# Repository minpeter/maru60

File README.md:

# Maru60

Maru60 is an experimental HHKB housing for Rule 60 V3 internals with an
integrated honeycomb wrist rest. This repository also includes the standalone
Rule 60 V3 wrist rest and an unfinished RP2350A PCB design.

| Start here | Contents |
| --- | --- |
| [Housing](docs/housing.md) | Build and verify matching top/bottom variants; print files, fit and assembly |
| [Physical build 02 — v7.15](docs/print-history.md) | Owner-designated second physical build: 6095, stock catches, inserts; final print pair and change record |
| [Standalone wrist rest](docs/wrist-rest.md) | Current tight-fit downloads, reproduction and print guidance |
| [PCB current state](pcb/CURRENT.md) | Strict baseline, development prototype and unresolved qualification |
| [PCB validation](docs/pcb-validation.md) | Reproduce native CAD, portable firmware and power checks |
| [PCB order package](pcb/order/README.md) | Gerbers, JLCPCB BOM and placement file for the order candidate, with ordering steps |
| [PCB fabrication draft](pcb/fabrication/README.md) | Earlier BOM, CPL and Gerbers for the 0/0 prototype; superseded by the order package |
| [Detailed fabrication reference](docs/fabrication.md) | Complete design history, measurements, hardware and plate guidance |

Install [uv](https://docs.astral.sh/uv/), then run from the repository root:

```sh
uv sync --locked
uv run python -m maru60.pipeline --board ph60-rev3
uv run python -m unittest discover -s tests
uv run tools/check_pcb_current.py
```

The housing pipeline builds and verifies both cases in a variant-specific
folder under `build/`. Both cases default to `--catches stock` with M2
self-tapping screw pilots (`--no-inserts`). Add `--catches luban32` for the
compatible LUBAN 32 mm ball catches (assumed widths, caliper first), `--inserts`
for CANOT M2 OD3.5 x L3 heat-set insert bores in both cases, or
`--no-battery-bay` for the wired lower case. Published `models/` and `evidence/`
change only with `--publish`; review [housing guidance](docs/housing.md) first.
CAD checks do not establish physical fit or strength. The custom PCB has an
[order candidate](pcb/order/README.md) for a first prototype run; it has **not
been built or qualified on hardware**.

The standalone wrist rest uses [CC BY 4.0](LICENSE); the Maru60 cases use
[CC BY-NC 4.0](LICENSE-topcase). See the [full license and design history](docs/fabrication.md#license-and-design-history)
for third-party exceptions and attribution.

<details>
<summary>Earlier README section links</summary>

[Rule 60 V3 Honeycomb Wrist Rest — No Extra Hardware](docs/fabrication.md#rule-60-v3-honeycomb-wrist-rest--no-extra-hardware) · 
[Download and print](docs/fabrication.md#download-and-print) · 
[Fit and assembly](docs/fabrication.md#fit-and-assembly) · 
[Slicing](docs/fabrication.md#slicing) · 
[Reproduce and continue designing](docs/fabrication.md#reproduce-and-continue-designing) · 
[Verification and limitations](docs/fabrication.md#verification-and-limitations) · 
[Maru60 HHKB top case with integrated wrist rest (experimental)](docs/fabrication.md#maru60-hhkb-top-case-with-integrated-wrist-rest-experimental) · 
[Printing](docs/fabrication.md#printing) · 
[Interface spec and PCB boards](docs/fabrication.md#interface-spec-and-pcb-boards) · 
[Reproduce](docs/fabrication.md#reproduce) · 
[Optional upper strike inserts (CANOT OD3.5 × L3 trial)](docs/fabrication.md#optional-upper-strike-inserts-canot-od35--l3-trial) · 
[Measurements and evidence](docs/fabrication.md#measurements-and-evidence) · 
[Verification and limitations](docs/fabrication.md#verification-and-limitations-1) · 
[Maru60 HHKB bottom case (draft)](docs/fabrication.md#maru60-hhkb-bottom-case-draft) · 
[Local M2 insert-mount study (not released)](docs/fabrication.md#local-m2-insert-mount-study-not-released) · 
[Purchased 32 mm catches / CANOT inserts — separate local trial](docs/fabrication.md#purchased-32-mm-catches--canot-inserts--separate-local-trial) · 
[Photo-refined sculpted alternative (C-derived, still experimental)](docs/fabrication.md#photo-refined-sculpted-alternative-c-derived-still-experimental) · 
[HHKB gasket plate (INKC drawing)](docs/fabrication.md#hhkb-gasket-plate-inkc-drawing) · 
[PCB](docs/fabrication.md#pcb) · 
[Off-the-shelf board: PH60 Rev.3 Multi](docs/fabrication.md#off-the-shelf-board-ph60-rev3-multi) · 
[Maru60's own PCB (RP2350A, work in progress)](docs/fabrication.md#maru60s-own-pcb-rp2350a-work-in-progress) · 
[License and design history](docs/fabrication.md#license-and-design-history)

</details>

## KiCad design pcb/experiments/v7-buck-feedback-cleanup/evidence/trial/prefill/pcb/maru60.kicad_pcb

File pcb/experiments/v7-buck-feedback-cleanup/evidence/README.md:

# BUCK_FB dead-arm experiment: UNSELECTED, strict global plane gate FAIL

This packet preserves the exact selected 2c7 source project, unselected aead dead-arm cleanup, native prefill/filled diagnostics, source-bound plan, independent strict rejection, and separate no-edit/repeat normal-refill controls. No selection, tolerance waiver, manual fill repair, noise reduction, loop-stability, hardware or manufacturing qualification is implied.

Read trial/TECHNICAL_REVIEW.md first. The independent-strict-review packet is included unchanged with its own manifest. Read CASE_SPECIFIC_ENGINEERING_DECISION.md for the separate case-specific precision condition. It does not retroactively change the original strict rejection; independent precision proof and fresh final rechecks are separate evidence. Both normal-refill controls are byte-identical fixed points; the real remote saved-contour losses remain.

Scripts preserve their original absolute paths and exact source-hash assertions. For replay on another machine, map the original /tmp/v7-buck-deadarm-trial-2c7e to trial/, the plan and control directories to the corresponding bundled folders, and the selected repository project to trial/source/pcb/. KiCad 9.0.2+dfsg-1 and Python pcbnew are required. Runtime caches are excluded; native evidence and failed/interrupted diagnostic records are retained. Do not replay scripts against the selected project without isolation. The source-bound CAD is supplied directly, not reconstructed from a report.

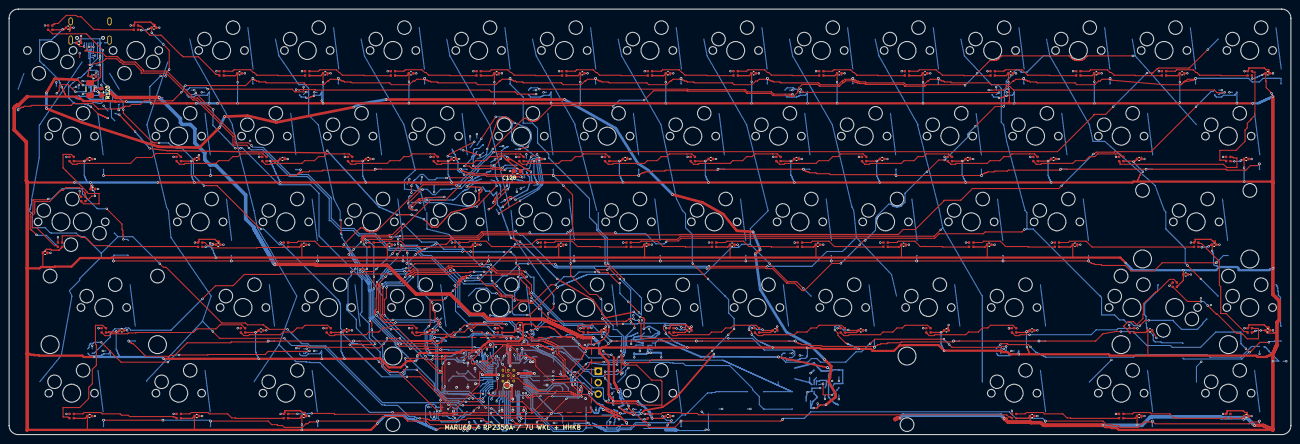
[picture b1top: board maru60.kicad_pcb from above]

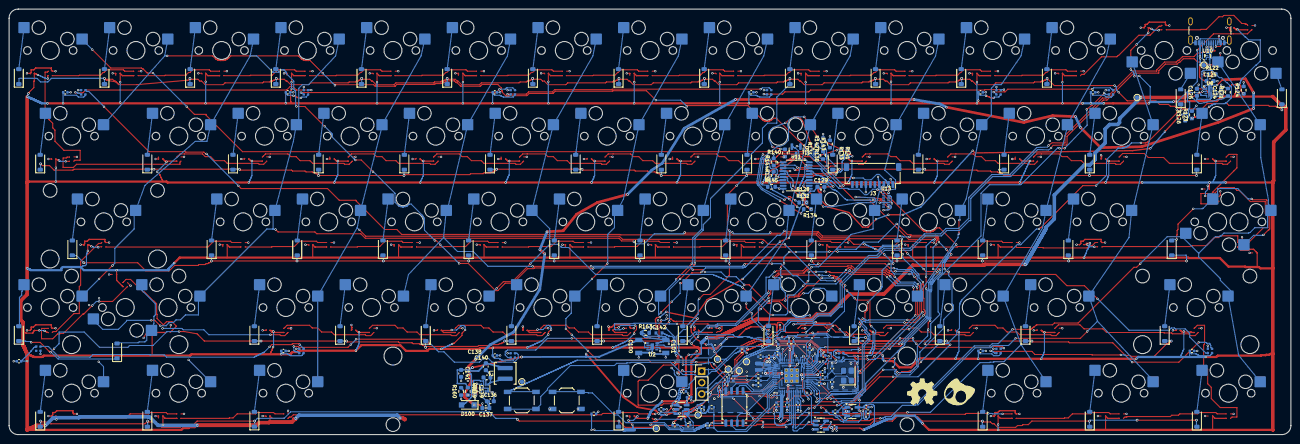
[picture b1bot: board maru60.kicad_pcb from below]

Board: 4 copper layers, 285.0 x 94.6 mm, 382 parts (247 on the bottom side), 224 nets.

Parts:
C100, C101: 4.7uF 50V X7R 10%; Murata_GRM31_1206_Reflow_1.0x1.6_Gap1.9
C102, C103: 4.7u 6.3V; C_0402_Official_R4_Wide
C104: 4.7u 6.3V; C_0402_1005Metric
C105, C108, C110, C111, C112, C113, C114, C115, C116, C117, C118, C122, C123, C199: 100n; C_0402_1005Metric
C106, C107: 15p C0G; C_0402_1005Metric
C109: 4.7u 6.3V X5R; C_0402_1005Metric
C120: 1u; C_0402_1005Metric
C121: 4.7u; C_0402_1005Metric
C124: 10nF 10% 50V; C_0603_1608Metric
C125: 1uF 50V effective TBD; C_0603_1608Metric
C126: 1uF 50V; C_0603_1608Metric
C128, C129: 100nF 16V; C_0603_1608Metric
C136: 100nF 50V; C_0603_1608Metric
C137: 4.7uF 50V effective>=2uF TBD; C_0603_1608Metric
C138: 100nF 16V BST-SW; C_0603_1608Metric
C139: 100nF 10% 16V - soft start; C_0603_1608Metric
C140, C141: 22uF 10V effective>=12uF TBD; C_0603_1608Metric
C142: 10nF 50V C0G 5%; Murata_GRM18_0603_Reflow_0.65x0.75_Gap0.7
C200, C201, C202, C203, C204, C205, C206, C207, C208, C209, C210, C211, C212, C213, C214, C215, C216, C217, C218, C219, C220, C221, C222, C223, C224, C225, C226, C227, C228, C229, C230, C231, C232, C233, C234, C235, C236, C237, C238, C239, C240, C241, C242, C243, C244, C245, C246, C247, C248, C249, C250, C251, C252, C253, C254, C255, C256, C257, C258, C259, C260, C261, C262, C263, C264, C265, C266, C267, C268, C269, C270, C271, C272, C273: 100nF; C_0402_1005Metric
C274, C275: 100nF 10V X7R candidate; C_0402_1005Metric
D1, D2, D3, D4, D5, D6, D7, D8, D9, D10, D11, D12, D13, D14, D15, D16, D17, D18, D19, D20, D21, D22, D23, D24, D25, D26, D27, D28, D29, D30, D31, D32, D33, D34, D35, D36, D37, D38, D39, D40, D41, D42, D43, D44, D45, D46, D47, D48, D49, D50, D51, D52, D53, D54, D55, D56, D57, D58, D59, D60, D61, D62: 1N4148W; D_SOD-123
D100: PMEG4030ER - reverse discharge bypass; Nexperia_CFP3_SOD-123W
F1: SF-1206F100-2 CANDIDATE; Fuse_1206_3216Metric
J1: USB4105-GF-A (candidate); USB_C_Receptacle_GCT_USB4105-xx-A_16P_TopMnt_Horizontal
J2: SWD / GND / SWCLK; PinHeader_1x03_P2.54mm_Vertical
J3: SM10B-SRSS-TB; JST_SH_SM10B-SRSS-TB_1x10-1MP_P1.00mm_Horizontal
L1: 3.3uH AOTA-B201610S3R3-101-T; Abracon_AOTA_B201610S3R3_Official_R4
L2: XAL4030-472MEC 4.7uH 20%; L_Coilcraft_XAL4030-XXX
LED1, LED2, LED3, LED4, LED5, LED6, LED7, LED8, LED9, LED10, LED11, LED12, LED13, LED14, LED15, LED16, LED17, LED18, LED19, LED20, LED21, LED22, LED23, LED24, LED25, LED26, LED27, LED28, LED29, LED30, LED31, LED32, LED33, LED34, LED35, LED36, LED37, LED38, LED39, LED40, LED41, LED42, LED43, LED44, LED45, LED46, LED47, LED48, LED49, LED50, LED51, LED52, LED53, LED54, LED55, LED56, LED57, LED58, LED59, LED60, LED61, LED62, LED63, LED64, LED65, LED66, LED67, LED68, LED69, LED70, LED71, LED72, LED73, LED74, LED75, LED76: SK6805-EC15-001; LED_SK6805_EC15_001_Recommended_Candidate
LOGO1: OSHW + minpeter character — DRAFT; OSHW_then_Minpeter_H6_Gap1p5_Silk_DRAFT
R100, R101: 5.1k 1%; R_0402_1005Metric
R102, R103: 27; R_0402_1005Metric
R104: 33; R_0402_1005Metric
R105, R113, R114: 10k; R_0402_1005Metric
R106, R107, R108: 1k; R_0402_1005Metric
R109: 100k; R_0402_1005Metric
R110, R111: 330; R_0402_1005Metric
R112: 133k 1%; R_0402_1005Metric
R120: 590k 0.1%; R_0603_1608Metric
R121: 156k 0.1%; R_0603_1608Metric
R122: 620k 0.1%; R_0603_1608Metric
R123: 267k 0.1%; R_0603_1608Metric
R124: 6.65k 0.1%; R_0603_1608Metric
R126, R128: 100k 1%; R_0603_1608Metric
R130, R131, R132, R133, R134, R135: 1.00k 1%; R_0603_1608Metric
R140, R141, R142, R143, R144, R145: 39.0k 1%; R_0603_1608Metric
R159: 40.0k 0.1%; R_0603_1608Metric
R160: 10.0k 0.1%; R_0603_1608Metric
R163: 31.6k 0.1% 10ppm/K; R_0603_1608Metric
STAB_RS1: (no value)
SW1: Esc; MX-Hotswap-1U
SW2: 1; MX-Hotswap-1U
SW3: 2; MX-Hotswap-1U
SW4: 3; MX-Hotswap-1U
SW5: 4; MX-Hotswap-1U
SW6: 5; MX-Hotswap-1U
SW7: 6; MX-Hotswap-1U
SW8: 7; MX-Hotswap-1U
SW9: 8; MX-Hotswap-1U
SW10: 9; MX-Hotswap-1U
SW11: 0; MX-Hotswap-1U
SW12: Minus; MX-Hotswap-1U
SW13: Equal; MX-Hotswap-1U
SW14: Backspace_L; MX-Hotswap-1U
SW15: Backspace_R; MX-Hotswap-1U
SW16: Tab; MX-Hotswap-1U
SW17: Q; MX-Hotswap-1U
SW18: W; MX-Hotswap-1U
SW19: E; MX-Hotswap-1U
SW20: R; MX-Hotswap-1U
SW21: T; MX-Hotswap-1U
SW22: Y; MX-Hotswap-1U
SW23: U; MX-Hotswap-1U
SW24: I; MX-Hotswap-1U
SW25: O; MX-Hotswap-1U
SW26: P; MX-Hotswap-1U
SW27: LeftBracket; MX-Hotswap-1U
SW28: RightBracket; MX-Hotswap-1U
SW29: Backslash; MX-Hotswap-1U
SW31: A; MX-Hotswap-1U
SW32: S; MX-Hotswap-1U
SW33: D; MX-Hotswap-1U
SW34: F; MX-Hotswap-1U
SW35: G; MX-Hotswap-1U
SW36: H; MX-Hotswap-1U
SW37: J; MX-Hotswap-1U
SW38: K; MX-Hotswap-1U
SW39: L; MX-Hotswap-1U
SW40: Semicolon; MX-Hotswap-1U
SW41: Quote; MX-Hotswap-1U
SW42: Enter; MX-Hotswap-2.25U-4L-NPTH
SW43: LeftShift; MX-Hotswap-2.25U-4L-NPTH
SW44: Z; MX-Hotswap-1U
SW45: X; MX-Hotswap-1U
SW46: C; MX-Hotswap-1U
SW47: V; MX-Hotswap-1U
SW48: B; MX-Hotswap-1U
SW49: N; MX-Hotswap-1U
SW50: M; MX-Hotswap-1U
SW51: Comma; MX-Hotswap-1U
SW52: Period; MX-Hotswap-1U
SW53: Slash; MX-Hotswap-1U
SW56: LCtrl; MX-Hotswap-1U
SW57: LMeta; MX-Hotswap-1U
SW58: LAlt; MX-Hotswap-1U
SW59: Space; MX-Hotswap-7U-4L-NPTH-StabRot180
SW60: RAlt; MX-Hotswap-1U
SW61: RMeta; MX-Hotswap-1U
SW62: RCtrl; MX-Hotswap-1U
SW100: BOOTSEL; SW_SPST_TL3342
SW101: RESET; SW_SPST_TL3342
SWCAP1: Caps_Options; MX_Study_Caps_Normal_or_Stepped
SWRS1: RShift_Options; MX_Study_RShift_2.75U_or_1.75U_1U
TP1: GND TEST; TestPoint_Pad_D1.0mm
TP2: VBUS TEST; TestPoint_Pad_D1.0mm
TP3: +4V TEST; TestPoint_Pad_D1.0mm
TP4: +3V3 TEST; TestPoint_Pad_D1.0mm
TP5: +1V1 TEST; TestPoint_Pad_D1.0mm
TP6: RUN TEST; TestPoint_Pad_D1.0mm
TP7: SWDIO TEST; TestPoint_Pad_D1.0mm
TP8: SWCLK TEST; TestPoint_Pad_D1.0mm
TP9: LED_FAULT_N TEST; TestPoint_Pad_D1.0mm
TP10: +4V_LED TEST; TestPoint_Pad_D1.0mm
U1: RP2350A (A4 required); RP2350A_QFN60_Official_R4
U2: MAX38902AATA+T; MAX_T822-3C_90-0065_2x2_P0.5_EP0.8x1.38
U3: W25Q32JVSSIQ (4MiB); SOIC-8_5.3x5.3mm_P1.27mm
U5, U6: SN74LV1T125DBVR; SOT-23-5
U7: TPS2553DBVR-1; SOT-23-6
U8: TPS259470LRPW; TI_RPW0010A_2x2mm_Official4225183A_DRAFT
U10: TPD2EUSB30DRTR; Texas_DRT-3
U11: SN74CB3T3245PWR; Texas_PW0020A_TSSOP-20_4.4x6.5mm_P0.65mm
U12: TLV810EA29DBZR; SOT-23
U13: TPD6E05U06RVZR; TI_RVZ14_1p35x3p5mm_P0p5_DERIVED_DRAFT
U18: TPS62932DRLR; SOT-583-8
Y1: 12MHz ABM8-272-T3; Crystal_SMD_3225-4Pin_3.2x2.5mm

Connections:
+1V1: C103.1, C108.1, C109.1, C110.1, L1.1, TP5.1, U1.6, U1.23, U1.39, U1.50
+3V3: C101.1, C102.1, C105.1, C111.1, C112.1, C113.1, C114.1, C115.1, C116.1, C117.1, C118.1, C128.1, C129.1, C142.1, C199.1, R104.1, R105.1, R113.1, R126.2, R128.2, R163.1, TP4.1, U1.1, U1.11, U1.20, U1.30, U1.38, U1.44, U1.45, U1.49, U1.53, U1.54, U2.6, U2.8, U3.8, U11.20, U12.3
+4V_LED: C121.1, C122.1, C123.1, C200.1, C201.1, C202.1, C203.1, C204.1, C205.1, C206.1, C207.1, C208.1, C209.1, C210.1, C211.1, C212.1, C213.1, C214.1, C215.1, C216.1, C217.1, C218.1, C219.1, C220.1, C221.1, C222.1, C223.1, C224.1, C225.1, C226.1, C227.1, C228.1, C229.1, C230.1, C231.1, C232.1, C233.1, C234.1, C235.1, C236.1, C237.1, C238.1, C239.1, C240.1, C241.1, C242.1, C243.1, C244.1, C245.1, C246.1, C247.1, C248.1, C249.1, C250.1, C251.1, C252.1, C253.1, C254.1, C255.1, C256.1, C257.1, C258.1, C259.1, C260.1, C261.1, C262.1, C263.1, C264.1, C265.1, C266.1, C267.1, C268.1, C269.1, C270.1, C271.1, C272.1, C273.1, C274.1, C275.1, LED1.2, LED2.2, LED3.2, LED4.2, LED5.2, LED6.2, LED7.2, LED8.2, LED9.2, LED10.2, LED11.2, LED12.2, LED13.2, LED14.2, LED15.2, LED16.2, LED17.2, LED18.2, LED19.2, LED20.2, LED21.2, LED22.2, LED23.2, LED24.2, LED25.2, LED26.2, LED27.2, LED28.2, LED29.2, LED30.2, LED31.2, LED32.2, LED33.2, LED34.2, LED35.2, LED36.2, LED37.2, LED38.2, LED39.2, LED40.2, LED41.2, LED42.2, LED43.2, LED44.2, LED45.2, LED46.2, LED47.2, LED48.2, LED49.2, LED50.2, LED51.2, LED52.2, LED53.2, LED54.2, LED55.2, LED56.2, LED57.2, LED58.2, LED59.2, LED60.2, LED61.2, LED62.2, LED63.2, LED64.2, LED65.2, LED66.2, LED67.2, LED68.2, LED69.2, LED70.2, LED71.2, LED72.2, LED73.2, LED74.2, LED75.2, LED76.2, R114.1, TP10.1, U5.5, U6.5, U7.6
+4V_REG: C100.1, C120.1, C140.1, C141.1, D100.2, L2.2, R159.1, TP3.1, U2.1, U2.3, U7.1
BOOT_BUTTON: R106.2, SW100.1
BUCK_BST: C138.1, U18.6
BUCK_FB: R159.2, R160.1, U18.8
BUCK_SS: C139.1, U18.7
BUCK_SW: C138.2, L2.1, U18.5
CC1: J1.A5, R100.1
CC2: J1.B5, R101.1
COL0: SW1.1, SW16.1, SW43.1, SW56.1, SWCAP1.1, SWCAP1.3, U1.8
COL1: SW2.1, SW17.1, SW31.1, SW44.1, SW57.1, U1.9
COL2: SW3.1, SW18.1, SW32.1, SW45.1, SW58.1, U1.10
COL3: SW4.1, SW19.1, SW33.1, SW46.1, U1.12
COL4: SW5.1, SW20.1, SW34.1, SW47.1, U1.13
COL5: SW6.1, SW21.1, SW35.1, SW48.1, U1.42
COL6: SW7.1, SW22.1, SW36.1, SW49.1, SW59.1, U1.15
COL7: SW8.1, SW23.1, SW37.1, SW50.1, U1.16
COL8: SW9.1, SW24.1, SW38.1, SW51.1, U1.17
COL9: SW10.1, SW25.1, SW39.1, SW52.1, U1.18
COL10: SW11.1, SW26.1, SW40.1, SW53.1, SW60.1, U1.19
COL11: SW12.1, SW27.1, SW41.1, SW61.1, SWRS1.1, SWRS1.3, U1.27
COL12: SW13.1, SW28.1, SW42.1, SW62.1, SWRS1.5, U1.28
COL13: SW14.1, SW29.1, U1.29
COL14: SW15.1, U1.31
EXT_GPIO3: J3.2, U11.18, U13.14
EXT_GPIO10: J3.3, U11.17, U13.13
EXT_GPIO24: J3.5, U11.16, U13.12
EXT_GPIO25: J3.6, U11.15, U13.11
EXT_GPIO26: J3.8, U11.14, U13.9
EXT_GPIO27: J3.9, U11.13, U13.8
GND: C100.2, C101.2, C102.2, C103.2, C104.2, C105.2, C106.2, C107.2, C108.2, C109.2, C110.2, C111.2, C112.2, C113.2, C114.2, C115.2, C116.2, C117.2, C118.2, C120.2, C121.2, C122.2, C123.2, C124.2, C125.2, C126.2, C128.2, C129.2, C136.2, C137.2, C139.2, C140.2, C141.2, C199.2, C200.2, C201.2, C202.2, C203.2, C204.2, C205.2, C206.2, C207.2, C208.2, C209.2, C210.2, C211.2, C212.2, C213.2, C214.2, C215.2, C216.2, C217.2, C218.2, C219.2, C220.2, C221.2, C222.2, C223.2, C224.2, C225.2, C226.2, C227.2, C228.2, C229.2, C230.2, C231.2, C232.2, C233.2, C234.2, C235.2, C236.2, C237.2, C238.2, C239.2, C240.2, C241.2, C242.2, C243.2, C244.2, C245.2, C246.2, C247.2, C248.2, C249.2, C250.2, C251.2, C252.2, C253.2, C254.2, C255.2, C256.2, C257.2, C258.2, C259.2, C260.2, C261.2, C262.2, C263.2, C264.2, C265.2, C266.2, C267.2, C268.2, C269.2, C270.2, C271.2, C272.2, C273.2, C274.2, C275.2, J1.A1, J1.A12, J1.B1, J1.B12, J1.S1, J2.2, J3.1, J3.4, J3.7, LED1.4, LED2.4, LED3.4, LED4.4, LED5.4, LED6.4, LED7.4, LED8.4, LED9.4, LED10.4, LED11.4, LED12.4, LED13.4, LED14.4, LED15.4, LED16.4, LED17.4, LED18.4, LED19.4, LED20.4, LED21.4, LED22.4, LED23.4, LED24.4, LED25.4, LED26.4, LED27.4, LED28.4, LED29.4, LED30.4, LED31.4, LED32.4, LED33.4, LED34.4, LED35.4, LED36.4, LED37.4, LED38.4, LED39.4, LED40.4, LED41.4, LED42.4, LED43.4, LED44.4, LED45.4, LED46.4, LED47.4, LED48.4, LED49.4, LED50.4, LED51.4, LED52.4, LED53.4, LED54.4, LED55.4, LED56.4, LED57.4, LED58.4, LED59.4, LED60.4, LED61.4, LED62.4, LED63.4, LED64.4, LED65.4, LED66.4, LED67.4, LED68.4, LED69.4, LED70.4, LED71.4, LED72.4, LED73.4, LED74.4, LED75.4, LED76.4, R100.2, R101.2, R107.2, R109.2, R112.2, R114.2, R121.2, R123.2, R124.2, R140.2, R141.2, R142.2, R143.2, R144.2, R145.2, R160.2, R163.2, SW100.2, TP1.1, U1.47, U1.61, U2.2, U2.4, U2.9, U3.4, U5.1, U5.3, U6.1, U6.3, U7.2, U8.8, U10.3, U11.10, U12.1, U13.5, U13.10, U18.4, Y1.2, Y1.4
GPIO3_ISO: R130.2, U11.2
GPIO10_ISO: R131.2, U11.3
GPIO24_ISO: R132.2, U11.4
GPIO25_ISO: R133.2, U11.5
GPIO26_ISO: R134.2, U11.6
GPIO27_ISO: R135.2, U11.7
GPIO_ISOLATE: R128.1, U11.19, U12.2
KEY_1: D1.2, SW1.2
KEY_2: D2.2, SW2.2
KEY_3: D3.2, SW3.2
KEY_4: D4.2, SW4.2
KEY_5: D5.2, SW5.2
KEY_6: D6.2, SW6.2
KEY_7: D7.2, SW7.2
KEY_8: D8.2, SW8.2
KEY_9: D9.2, SW9.2
KEY_10: D10.2, SW10.2
KEY_11: D11.2, SW11.2
KEY_12: D12.2, SW12.2
KEY_13: D13.2, SW13.2
KEY_14: D14.2, SW14.2
KEY_15: D15.2, SW15.2
KEY_16: D16.2, SW16.2
KEY_17: D17.2, SW17.2
KEY_18: D18.2, SW18.2
KEY_19: D19.2, SW19.2
KEY_20: D20.2, SW20.2
KEY_21: D21.2, SW21.2
KEY_22: D22.2, SW22.2
KEY_23: D23.2, SW23.2
KEY_24: D24.2, SW24.2
KEY_25: D25.2, SW25.2
KEY_26: D26.2, SW26.2
KEY_27: D27.2, SW27.2
KEY_28: D28.2, SW28.2
KEY_29: D29.2, SW29.2
KEY_30: D30.2, SWCAP1.2, SWCAP1.4
KEY_31: D31.2, SW31.2
KEY_32: D32.2, SW32.2
KEY_33: D33.2, SW33.2
KEY_34: D34.2, SW34.2
KEY_35: D35.2, SW35.2
KEY_36: D36.2, SW36.2
KEY_37: D37.2, SW37.2
KEY_38: D38.2, SW38.2
KEY_39: D39.2, SW39.2
KEY_40: D40.2, SW40.2
KEY_41: D41.2, SW41.2
KEY_42: D42.2, SW42.2
KEY_43: D43.2, SW43.2
KEY_44: D44.2, SW44.2
KEY_45: D45.2, SW45.2
KEY_46: D46.2, SW46.2
KEY_47: D47.2, SW47.2
KEY_48: D48.2, SW48.2
KEY_49: D49.2, SW49.2
KEY_50: D50.2, SW50.2
KEY_51: D51.2, SW51.2
KEY_52: D52.2, SW52.2
KEY_53: D53.2, SW53.2
KEY_54: D54.2, SWRS1.2, SWRS1.4
KEY_55: D55.2, SWRS1.6
KEY_56: D56.2, SW56.2
KEY_57: D57.2, SW57.2
KEY_58: D58.2, SW58.2
KEY_59: D59.2, SW59.2
KEY_60: D60.2, SW60.2
KEY_61: D61.2, SW61.2
KEY_62: D62.2, SW62.2
KEY_RGB: U1.32, U5.2
KEY_RGB_5V: LED1.1, R110.2
KEY_RGB_5V_BUF: R110.1, U5.4
KEY_RGB_CHAIN_1: LED1.3, LED2.1
KEY_RGB_CHAIN_2: LED2.3, LED3.1
KEY_RGB_CHAIN_3: LED3.3, LED4.1
KEY_RGB_CHAIN_4: LED4.3, LED5.1
KEY_RGB_CHAIN_5: LED5.3, LED6.1
KEY_RGB_CHAIN_6: LED6.3, LED7.1
KEY_RGB_CHAIN_7: LED7.3, LED8.1
KEY_RGB_CHAIN_8: LED8.3, LED9.1
KEY_RGB_CHAIN_9: LED9.3, LED10.1
KEY_RGB_CHAIN_10: LED10.3, LED11.1
KEY_RGB_CHAIN_11: LED11.3, LED12.1
KEY_RGB_CHAIN_12: LED12.3, LED13.1
KEY_RGB_CHAIN_13: LED13.3, LED14.1
KEY_RGB_CHAIN_14: LED14.3, LED15.1
KEY_RGB_CHAIN_15: LED15.3, LED29.1
KEY_RGB_CHAIN_16: LED28.1, LED29.3
KEY_RGB_CHAIN_17: LED27.1, LED28.3
KEY_RGB_CHAIN_18: LED26.1, LED27.3
KEY_RGB_CHAIN_19: LED25.1, LED26.3
KEY_RGB_CHAIN_20: LED24.1, LED25.3
KEY_RGB_CHAIN_21: LED23.1, LED24.3
KEY_RGB_CHAIN_22: LED22.1, LED23.3
KEY_RGB_CHAIN_23: LED21.1, LED22.3
KEY_RGB_CHAIN_24: LED20.1, LED21.3
KEY_RGB_CHAIN_25: LED19.1, LED20.3
KEY_RGB_CHAIN_26: LED18.1, LED19.3
KEY_RGB_CHAIN_27: LED17.1, LED18.3
KEY_RGB_CHAIN_28: LED16.1, LED17.3
KEY_RGB_CHAIN_29: LED16.3, LED30.1
KEY_RGB_CHAIN_30: LED30.3, LED75.1
KEY_RGB_CHAIN_31: LED31.1, LED75.3
KEY_RGB_CHAIN_32: LED31.3, LED32.1
KEY_RGB_CHAIN_33: LED32.3, LED33.1
KEY_RGB_CHAIN_34: LED33.3, LED34.1
KEY_RGB_CHAIN_35: LED34.3, LED35.1
KEY_RGB_CHAIN_36: LED35.3, LED36.1
KEY_RGB_CHAIN_37: LED36.3, LED37.1
KEY_RGB_CHAIN_38: LED37.3, LED38.1
KEY_RGB_CHAIN_39: LED38.3, LED39.1
KEY_RGB_CHAIN_40: LED39.3, LED40.1
KEY_RGB_CHAIN_41: LED40.3, LED41.1
KEY_RGB_CHAIN_42: LED41.3, LED42.1
KEY_RGB_CHAIN_43: LED42.3, LED55.1
KEY_RGB_CHAIN_44: LED55.3, LED76.1
KEY_RGB_CHAIN_45: LED54.1, LED76.3
KEY_RGB_CHAIN_46: LED53.1, LED54.3
KEY_RGB_CHAIN_47: LED52.1, LED53.3
KEY_RGB_CHAIN_48: LED51.1, LED52.3
KEY_RGB_CHAIN_49: LED50.1, LED51.3
KEY_RGB_CHAIN_50: LED49.1, LED50.3
KEY_RGB_CHAIN_51: LED48.1, LED49.3
KEY_RGB_CHAIN_52: LED47.1, LED48.3
KEY_RGB_CHAIN_53: LED46.1, LED47.3
KEY_RGB_CHAIN_54: LED45.1, LED46.3
KEY_RGB_CHAIN_55: LED44.1, LED45.3
KEY_RGB_CHAIN_56: LED43.1, LED44.3
KEY_RGB_CHAIN_57: LED43.3, LED56.1
KEY_RGB_CHAIN_58: LED56.3, LED57.1
KEY_RGB_CHAIN_59: LED57.3, LED58.1
KEY_RGB_CHAIN_60: LED58.3, LED59.1
KEY_RGB_CHAIN_61: LED59.3, LED60.1
KEY_RGB_CHAIN_62: LED60.3, LED61.1
KEY_RGB_CHAIN_63: LED61.3, LED62.1
LDO_BYP: C142.2, U2.7
LED_ENABLE: R109.1, U1.34, U7.3
LED_FAULT_N: R113.2, TP9.1, U1.35, U7.4
LED_ILIM: R112.1, U7.5
MCU_GPIO3: R130.1, R140.1, U1.5
MCU_GPIO10: R131.1, R141.1, U1.14
MCU_GPIO24: R132.1, R142.1, U1.36
MCU_GPIO25: R133.1, R143.1, U1.37
MCU_GPIO26: R134.1, R144.1, U1.40
MCU_GPIO27: R135.1, R145.1, U1.41
QSPI_SCLK: U1.56, U3.6
QSPI_SD0: U1.57, U3.5
QSPI_SD1: U1.59, U3.2
QSPI_SD2: U1.58, U3.3
QSPI_SD3: U1.55, U3.7
QSPI_SS: R105.2, R106.1, U1.60, U3.1
RESET_GND: R107.1, SW101.2
ROW0: D1.1, D2.1, D3.1, D4.1, D5.1, D6.1, D7.1, D8.1, D9.1, D10.1, D11.1, D12.1, D13.1, D14.1, D15.1, U1.2
ROW1: D16.1, D17.1, D18.1, D19.1, D20.1, D21.1, D22.1, D23.1, D24.1, D25.1, D26.1, D27.1, D28.1, D29.1, U1.3
ROW2: D30.1, D31.1, D32.1, D33.1, D34.1, D35.1, D36.1, D37.1, D38.1, D39.1, D40.1, D41.1, D42.1, U1.4
ROW3: D43.1, D44.1, D45.1, D46.1, D47.1, D48.1, D49.1, D50.1, D51.1, D52.1, D53.1, D54.1, D55.1, U1.43
ROW4: D56.1, D57.1, D58.1, D59.1, D60.1, D61.1, D62.1, U1.7
RUN: SW101.1, TP6.1, U1.26
SWCLK: J2.3, TP8.1, U1.24
SWDIO: J2.1, TP7.1, U1.25
UG_LED_1: LED63.3, LED64.1
UG_LED_2: LED64.3, LED65.1
UG_LED_3: LED65.3, LED66.1
UG_LED_4: LED66.3, LED67.1
UG_LED_5: LED67.3, LED68.1
UG_LED_6: LED68.3, LED69.1
UG_LED_7: LED69.3, LED70.1
UG_LED_8: LED70.3, LED71.1
UG_LED_9: LED71.3, LED72.1
UG_LED_10: LED72.3, LED73.1
UG_LED_11: LED73.3, LED74.1
UNDERGLOW: U1.33, U6.2
UNDERGLOW_5V: LED63.1, R111.2
UNDERGLOW_5V_BUF: R111.1, U6.4
USB_DM: R103.2, U1.51
USB_DM_CONN: J1.A7, J1.B7, R103.1, U10.2
USB_DP: R102.2, U1.52
USB_DP_CONN: J1.A6, J1.B6, R102.1, U10.1
USB_DVDT: C124.1, U8.7
USB_ILM: R124.1, U8.9
USB_INPUT_FAULT_N: R126.1, U8.4
USB_OVLO: R120.2, R121.1, U8.2
USB_UVLO: R122.2, R123.1, U8.1
VBUS: F1.1, J1.A4, J1.A9, J1.B4, J1.B9, TP2.1
VBUS_FUSED: C125.1, F1.2, R120.1, R122.1, U8.5
VBUS_PROTECTED_RAW: C126.1, C136.1, C137.1, D100.1, U8.6, U18.3
VREG_AVDD: C104.1, R104.2, U1.46
VREG_LX: L1.2, U1.48
XIN: C106.1, U1.21, Y1.1
XOUT: R108.2, U1.22
XTAL_OUT: C107.1, R108.1, Y1.3
